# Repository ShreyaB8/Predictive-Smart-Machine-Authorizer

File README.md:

<p align="center">
 
 <h1 align="center">Predictive Smart Machine Authorizer</h1>
</p>

### About the Project
We are building Smart Machine Authoriser to control access of the machines to monitor the health of every machine for a collective effort to automate the FabLab. The entire system will be easily manageable with all the data concisely presented on the front end and the logs from each machine kept in the database.

#### 1/5 projects of the Open Project series funded by SIIC, SRM IST.

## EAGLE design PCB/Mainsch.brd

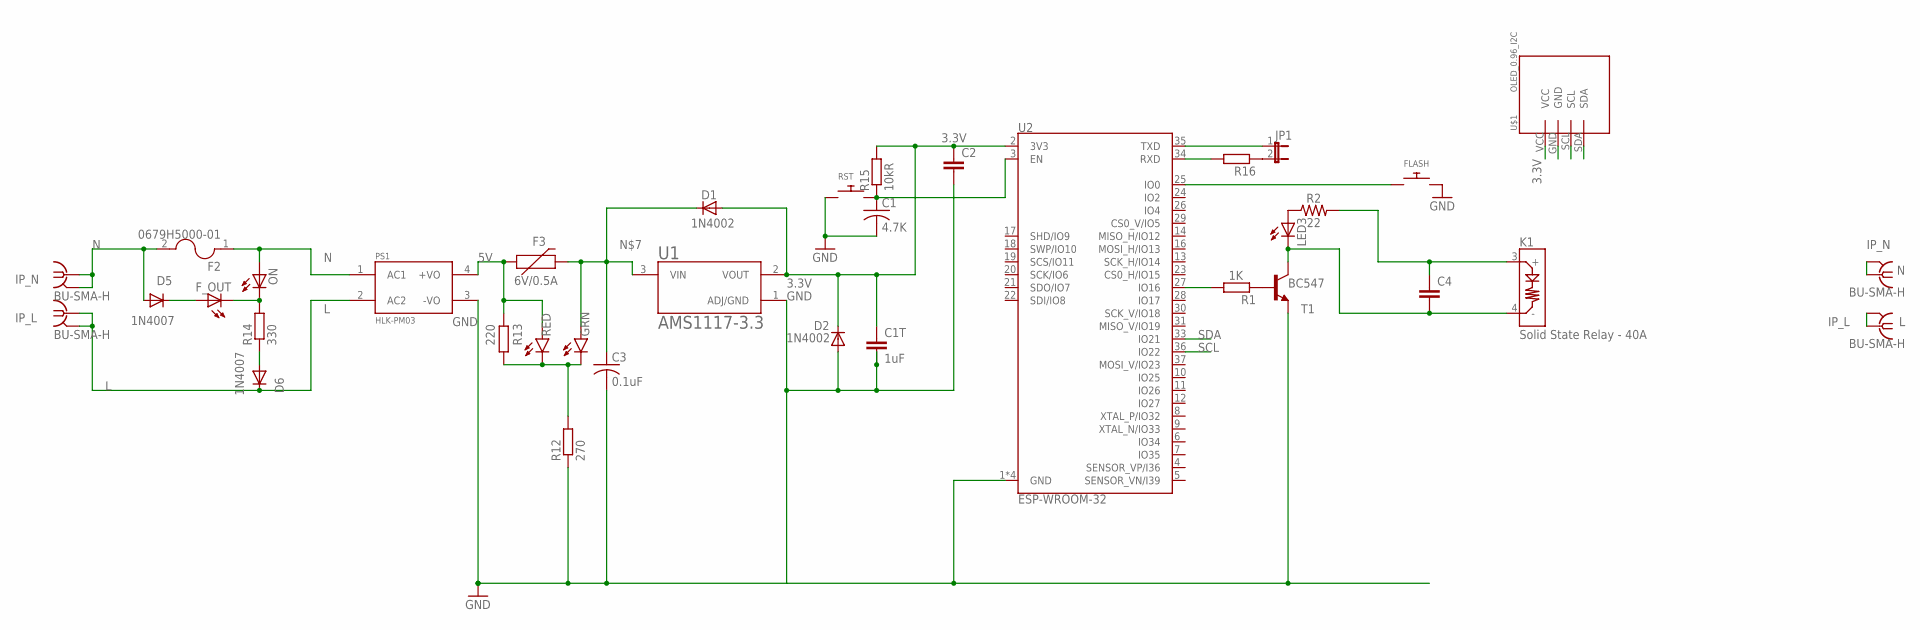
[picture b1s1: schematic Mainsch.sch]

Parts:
C1: 4.7K; C0805K
C1T: 1uF; C0805
C2, C4: C-EUC0805; C0805
C3: 0.1uF; C0805K
D1, D2: 1N4002; DO41-10
D5, D6: 1N4007; DO41-10
F2: 0679H5000-01; FUSC6125X279N
F3: 6V/0.5A; 1206
FLASH: SWITCH_PUSHBUTTONC&K_KSS; BTN_CK_KSS
F_OUT: LEDCHIPLED_1206; CHIPLED_1206
GRN: LED1206; LED-1206
IP_L: BU-SMA-H
IP_N: BU-SMA-H
JP1: JP1E; JP1
K1: Solid State Relay - 40A; SSR-40DA-H
L: BU-SMA-H
LED3: LEDCHIPLED_1206; CHIPLED_1206
N: BU-SMA-H
ON: LEDCHIPLED_1206; CHIPLED_1206
PS1: HLK-PM03; CONV_HLK-PM03
R1: 1K; R1206
R2: 22; 0603
R12: 270; R0805
R13: 220; R0805
R14: 330; R0805
R15: 10kR; R0805
R16: R-EU_R0805; R0805
RED: LED1206; LED-1206
RST: SWITCH_PUSHBUTTONC&K_KSS; BTN_CK_KSS
T1: BC547; TO92
U1: AMS1117-3.3; SOT229P700X180-4N
U2: ESP-WROOM-32
U$1: OLED_0.96_I2C

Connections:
3.3V: C1T.1, C2.1, D1.A, D2.C, R15.2, U1.2 (VOUT), U2.2 (3V3), U$1.VCC
5V: F3.1, PS1.4 (+VO), R13.2, RED.A
GND: C1.2, C1T.2, C2.2, C3.2, D2.A, FLASH.P$2, PS1.3 (-VO), R12.1, RST.P$1, T1.1 (E), U1.1 (ADJ/GND), U2.1 (GND), U2.15 (GND), U2.38 (GND), U2.GND, U$1.GND
IP_L: L.1, L.2, L.3 (2), L.4 (2), L.5 (2)
IP_N: N.1, N.2, N.3 (2), N.4 (2), N.5 (2)
L: D6.C, IP_L.1, IP_L.2, IP_L.3 (2), IP_L.4 (2), IP_L.5 (2), PS1.2 (AC2)
N: D5.A, F2.1, F2.2, IP_N.1, IP_N.2, IP_N.3 (2), IP_N.4 (2), IP_N.5 (2), ON.A, PS1.1 (AC1)
unnamed: JP1.2, R16.1
unnamed: C4.2, K1.4 (-), LED3.C, T1.3 (C)
unnamed: R1.2, U2.27 (IO16)
unnamed: LED3.A, R2.1
unnamed: D6.A, R14.1
unnamed: C3.1, D1.C, F3.2, GRN.A, U1.3 (VIN)
unnamed: JP1.1, U2.35 (TXD)
unnamed: R16.2, U2.34 (RXD)
unnamed: FLASH.P$1, U2.25 (IO0)
unnamed: C1.1, R15.1, RST.P$2, U2.3 (EN)
unnamed: R1.1, T1.2 (B)
unnamed: F_OUT.C, ON.C, R14.2
unnamed: D5.C, F_OUT.A
unnamed: GRN.C, R12.2, R13.1, RED.C
unnamed: C4.1, K1.3 (+), R2.2
SCL: U2.36 (IO22), U$1.SCL
SDA: U2.33 (IO21), U$1.SDA

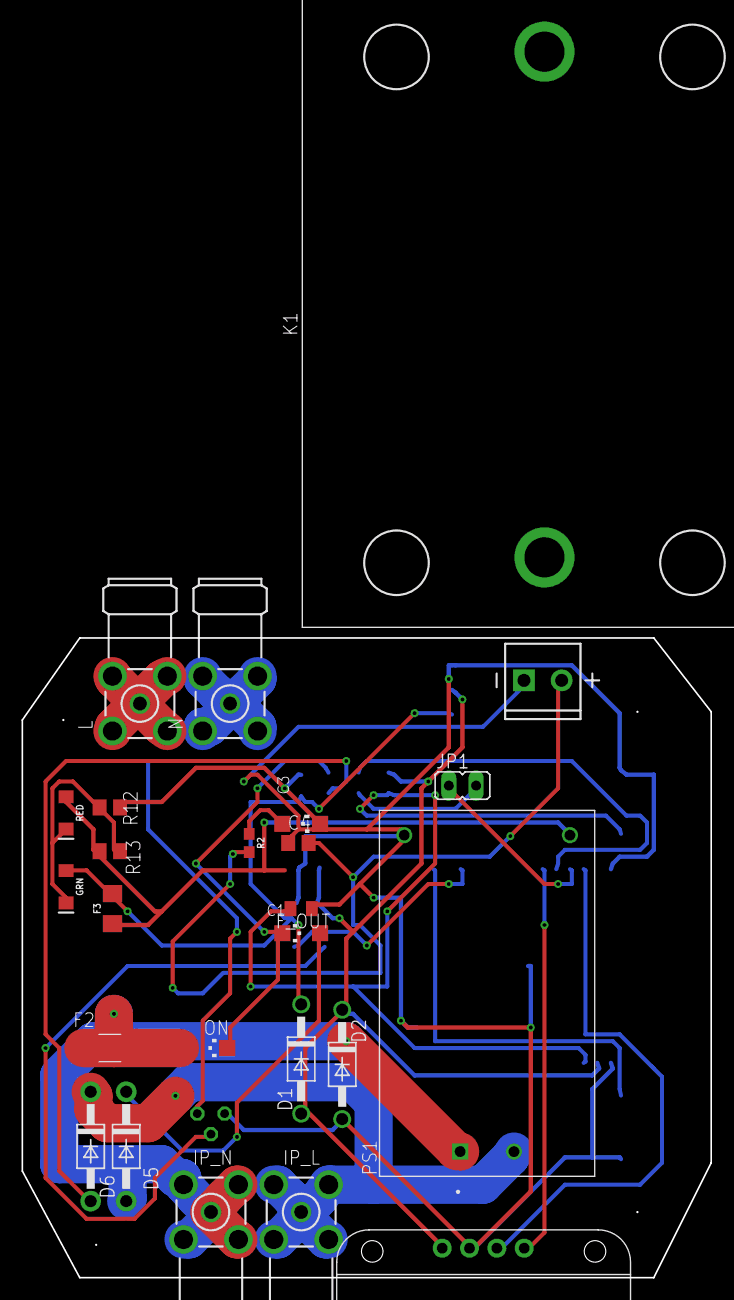
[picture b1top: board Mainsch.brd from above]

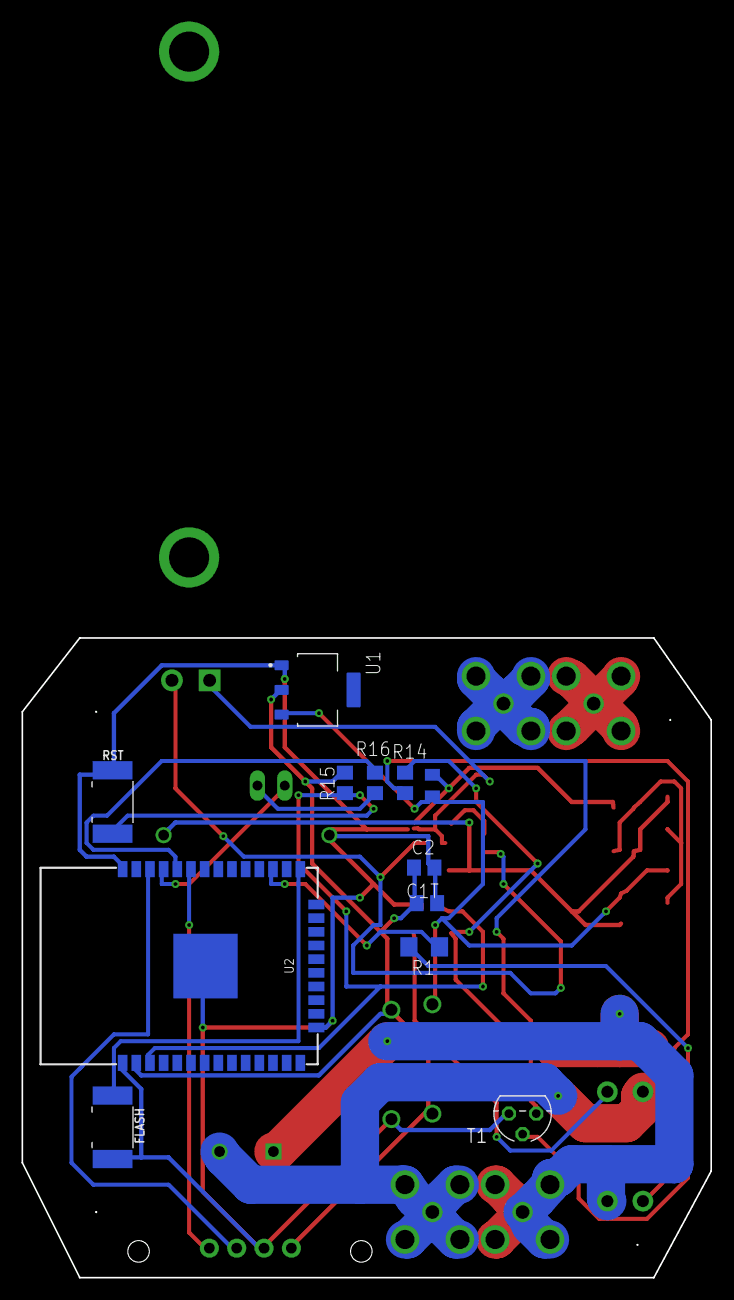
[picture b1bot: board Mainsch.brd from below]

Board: 2 copper layers, 64.0 x 59.4 mm, 36 parts (12 on the bottom side), 24 nets.

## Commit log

2020-06-08 Bump websocket-extensions from 0.1.3 to 0.1.4 in /functions
    Bumps [websocket-extensions](https://github.com/faye/websocket-extensions-node) from 0.1.3 to 0.1.4.
    - [Release notes](https://github.com/faye/websocket-extensions-node/releases)
    - [Changelog](https://github.com/faye/websocket-extensions-node/blob/master/CHANGELOG.md)
    - [Commits](https://github.com/faye/websocket-extensions-node/compare/0.1.3...0.1.4)
2020-06-26 updated webapp
2020-06-26 Bump minimist from 1.2.0 to 1.2.5 in /WA_Final
    Bumps [minimist](https://github.com/substack/minimist) from 1.2.0 to 1.2.5.
    - [Release notes](https://github.com/substack/minimist/releases)
    - [Commits](https://github.com/substack/minimist/compare/1.2.0...1.2.5)
2020-07-21 Bump lodash from 4.17.15 to 4.17.19 in /functions
    Bumps [lodash](https://github.com/lodash/lodash) from 4.17.15 to 4.17.19.
    - [Release notes](https://github.com/lodash/lodash/releases)
    - [Commits](https://github.com/lodash/lodash/compare/4.17.15...4.17.19)
2020-08-30 Bump minimist from 1.2.0 to 1.2.5
    Bumps [minimist](https://github.com/substack/minimist) from 1.2.0 to 1.2.5.
    - [Release notes](https://github.com/substack/minimist/releases)
    - [Commits](https://github.com/substack/minimist/compare/1.2.0...1.2.5)
2020-09-13 Bump node-fetch from 2.6.0 to 2.6.1 in /functions
    Bumps [node-fetch](https://github.com/bitinn/node-fetch) from 2.6.0 to 2.6.1.
    - [Release notes](https://github.com/bitinn/node-fetch/releases)
    - [Changelog](https://github.com/node-fetch/node-fetch/blob/master/docs/CHANGELOG.md)
    - [Commits](https://github.com/bitinn/node-fetch/compare/v2.6.0...v2.6.1)
2021-01-21 Bump socket.io from 2.3.0 to 2.4.0
    Bumps [socket.io](https://github.com/socketio/socket.io) from 2.3.0 to 2.4.0.
    - [Release notes](https://github.com/socketio/socket.io/releases)
    - [Changelog](https://github.com/socketio/socket.io/blob/2.4.0/CHANGELOG.md)
    - [Commits](https://github.com/socketio/socket.io/compare/2.3.0...2.4.0)
2021-05-11 Bump lodash from 4.17.15 to 4.17.21 in /functions
    Bumps [lodash](https://github.com/lodash/lodash) from 4.17.15 to 4.17.21.
    - [Release notes](https://github.com/lodash/lodash/releases)
    - [Commits](https://github.com/lodash/lodash/compare/4.17.15...4.17.21)
2021-06-30 Bump socket.io-parser from 3.3.0 to 3.3.2
    Bumps [socket.io-parser](https://github.com/socketio/socket.io-parser) from 3.3.0 to 3.3.2.
    - [Release notes](https://github.com/socketio/socket.io-parser/releases)
    - [Changelog](https://github.com/socketio/socket.io-parser/blob/3.3.2/CHANGELOG.md)
    - [Commits](https://github.com/socketio/socket.io-parser/compare/3.3.0...3.3.2)
    ---
    updated-dependencies:
2021-07-23 add sample data
2021-07-23 add MGD model
2021-10-21 Marzuk | Added Ble Sense Nano Code
2022-01-22 Bump node-fetch from 2.6.0 to 2.6.7 in /functions
    Bumps [node-fetch](https://github.com/node-fetch/node-fetch) from 2.6.0 to 2.6.7.
    - [Release notes](https://github.com/node-fetch/node-fetch/releases)
    - [Changelog](https://github.com/node-fetch/node-fetch/blob/main/docs/CHANGELOG.md)
    - [Commits](https://github.com/node-fetch/node-fetch/compare/v2.6.0...v2.6.7)
    ---
    updated-dependencies:
2022-02-13 Bump ajv from 6.12.0 to 6.12.6 in /functions
    Bumps [ajv](https://github.com/ajv-validator/ajv) from 6.12.0 to 6.12.6.
    - [Release notes](https://github.com/ajv-validator/ajv/releases)
    - [Commits](https://github.com/ajv-validator/ajv/compare/v6.12.0...v6.12.6)
    ---
    updated-dependencies:
    - dependency-name: ajv
2022-02-13 Bump ajv from 6.11.0 to 6.12.6
    Bumps [ajv](https://github.com/ajv-validator/ajv) from 6.11.0 to 6.12.6.
    - [Release notes](https://github.com/ajv-validator/ajv/releases)
    - [Commits](https://github.com/ajv-validator/ajv/compare/v6.11.0...v6.12.6)
    ---
    updated-dependencies:
    - dependency-name: ajv
2022-03-27 Bump minimist from 1.2.0 to 1.2.6
    Bumps [minimist](https://github.com/substack/minimist) from 1.2.0 to 1.2.6.
    - [Release notes](https://github.com/substack/minimist/releases)
    - [Commits](https://github.com/substack/minimist/compare/1.2.0...1.2.6)
    ---
    updated-dependencies:
    - dependency-name: minimist
2022-06-02 Bump protobufjs from 6.8.9 to 6.11.3 in /functions
    Bumps [protobufjs](https://github.com/protobufjs/protobuf.js) from 6.8.9 to 6.11.3.
    - [Release notes](https://github.com/protobufjs/protobuf.js/releases)
    - [Changelog](https://github.com/protobufjs/protobuf.js/blob/v6.11.3/CHANGELOG.md)
    - [Commits](https://github.com/protobufjs/protobuf.js/commits/v6.11.3)
    ---
    updated-dependencies:
2022-11-09 Bump socket.io-parser from 3.3.0 to 3.3.3
    Bumps [socket.io-parser](https://github.com/socketio/socket.io-parser) from 3.3.0 to 3.3.3.
    - [Release notes](https://github.com/socketio/socket.io-parser/releases)
    - [Changelog](https://github.com/socketio/socket.io-parser/blob/main/CHANGELOG.md)
    - [Commits](https://github.com/socketio/socket.io-parser/compare/3.3.0...3.3.3)
    ---
    updated-dependencies:
2022-11-23 Bump engine.io and socket.io
    Bumps [engine.io](https://github.com/socketio/engine.io) to 3.6.1 and updates ancestor dependency [socket.io](https://github.com/socketio/socket.io). These dependencies need to be updated together.
    Updates `engine.io` from 3.4.0 to 3.6.1
    - [Release notes](https://github.com/socketio/engine.io/releases)
    - [Changelog](https://github.com/socketio/engine.io/blob/main/CHANGELOG.md)
    - [Commits](https://github.com/socketio/engine.io/compare/3.4.0...3.6.1)
    Updates `socket.io` from 2.3.0 to 2.5.0
2022-12-07 Bump qs and express in /functions
    Bumps [qs](https://github.com/ljharb/qs) and [express](https://github.com/expressjs/express). These dependencies needed to be updated together.
    Updates `qs` from 6.7.0 to 6.11.0
    - [Release notes](https://github.com/ljharb/qs/releases)
    - [Changelog](https://github.com/ljharb/qs/blob/main/CHANGELOG.md)
    - [Commits](https://github.com/ljharb/qs/compare/v6.7.0...v6.11.0)
    Updates `express` from 4.17.1 to 4.18.2
2022-12-10 Bump express from 4.16.4 to 4.17.3
    Bumps [express](https://github.com/expressjs/express) from 4.16.4 to 4.17.3.
    - [Release notes](https://github.com/expressjs/express/releases)
    - [Changelog](https://github.com/expressjs/express/blob/master/History.md)
    - [Commits](https://github.com/expressjs/express/compare/4.16.4...4.17.3)
    ---
    updated-dependencies:
2022-12-11 Bump qs and express
    Bumps [qs](https://github.com/ljharb/qs) to 6.5.3 and updates ancestor dependency [express](https://github.com/expressjs/express). These dependencies need to be updated together.
    Updates `qs` from 6.5.2 to 6.5.3
    - [Release notes](https://github.com/ljharb/qs/releases)
    - [Changelog](https://github.com/ljharb/qs/blob/main/CHANGELOG.md)
    - [Commits](https://github.com/ljharb/qs/compare/v6.5.2...v6.5.3)
    Updates `express` from 4.16.4 to 4.18.2
2022-12-13 Bump express from 4.17.1 to 4.18.2 in /functions
    Bumps [express](https://github.com/expressjs/express) from 4.17.1 to 4.18.2.
    - [Release notes](https://github.com/expressjs/express/releases)
    - [Changelog](https://github.com/expressjs/express/blob/master/History.md)
    - [Commits](https://github.com/expressjs/express/compare/4.17.1...4.18.2)
    ---
    updated-dependencies:
2023-01-09 Bump jsonwebtoken, firebase-admin and firebase-functions in /functions
    Bumps [jsonwebtoken](https://github.com/auth0/node-jsonwebtoken) to 9.0.0 and updates ancestor dependencies [jsonwebtoken](https://github.com/auth0/node-jsonwebtoken), [firebase-admin](https://github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
    Updates `jsonwebtoken` from 8.1.0 to 9.0.0
    - [Release notes](https://github.com/auth0/node-jsonwebtoken/releases)
    - [Changelog](https://github.com/auth0/node-jsonwebtoken/blob/master/CHANGELOG.md)
    - [Commits](https://github.com/auth0/node-jsonwebtoken/compare/v8.1.0...v9

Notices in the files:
parts and their libraries:
SparkFun-DiscreteSemi: Licensing: Creative Commons ShareAlike 4.0 International - https://creativecommons.org/licenses/by-sa/4.0
